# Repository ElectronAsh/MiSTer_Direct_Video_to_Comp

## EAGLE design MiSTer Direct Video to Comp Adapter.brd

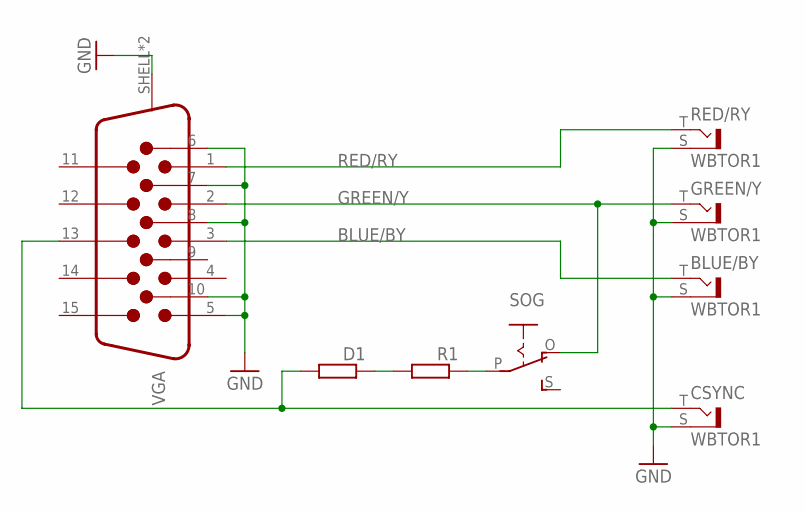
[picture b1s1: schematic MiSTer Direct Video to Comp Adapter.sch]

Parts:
BLUE/BY: WBTOR1
CSYNC: WBTOR1
D1: R-EU_R1206; R1206
GREEN/Y: WBTOR1
R1: R-EU_R0603; R0603
RED/RY: WBTOR1
SOG: EG1218S; EG1218
VGA: 618015331023

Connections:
BLUE/BY: BLUE/BY.T, VGA.3
GND: BLUE/BY.S, CSYNC.S, GREEN/Y.S, RED/RY.S, VGA.5, VGA.6, VGA.7, VGA.8, VGA.10, VGA.SHELL (SHIELD), VGA.SHELL1 (SHIELD)
GREEN/Y: GREEN/Y.T, SOG.O, VGA.2
unnamed: CSYNC.T, D1.2, VGA.13
unnamed: D1.1, R1.2
unnamed: R1.1, SOG.P
RED/RY: RED/RY.T, VGA.1

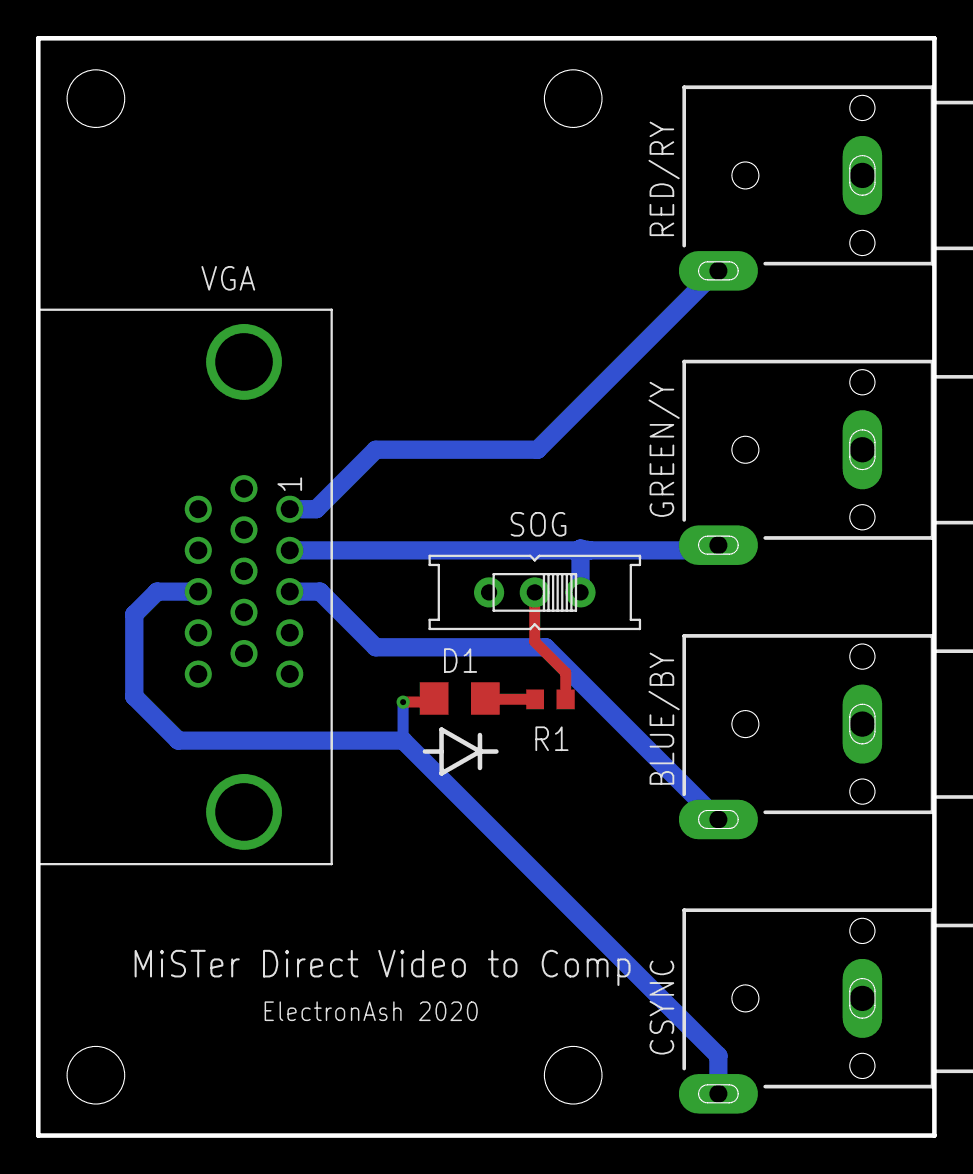
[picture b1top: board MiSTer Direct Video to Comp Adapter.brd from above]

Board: 2 copper layers, 49.8 x 61.0 mm, 8 parts (0 on the bottom side), 7 nets.

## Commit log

2020-01-15 added BOM CSV

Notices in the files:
parts and their libraries:
con-wurth: Copyright: Würth Elektronik
